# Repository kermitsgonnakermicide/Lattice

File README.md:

# Lattice

> a 60% mechanical keyboard with magnetically attached modules

# what even is Lattice?
Lattice is a modular 60% mechanical keyboard, with the main keyboard featuring:
- cherry mx black switches
- a raspberry pi pico 2
- an EC11 encoder
- 6 expansion ports(two 2.54 inch female headers and 4 4 pin magnetic pogo connectors)
- absolutely NO RGB(in the keyboard itself skdsks)

Lattice also comes with three modules(as of now), which are:
- a 16 key macropad with an OLED

- a 3 slider, two encoder module i'm calling the sliderpad

- a 32x4 RGB LED(specifically the WS2812B-2020) matrix that slides in the empty top bit of the keyboard(connected by 2.54 mm pins because I didnt trust the current limits of the magnetic connectors)

Each module features a xiao rp2040 to run everything else on it because its so smol and cute :3</br>

The macropad and the sliderpad connect with magnetic pogo pins and use I2C to communicate with the main board, while the matrix does the same thing but just connects with normal pin headers and sockets. </br>

in terms of firmware, I have something basic for now - which runs each individual board and packs the data for I2C into a 16 bit struct - this wasnt really tracked as I lowk forgot and I used a bunch of AI so I wouldnt want track it anyways

# why did you even build this?(and many other whys)
I lowkenuinely just needed a keyboard pretty desperately - i've been using my crusty musty dusty redragon k552 for almost 5 years now and I need to switch it out :cryin:
additionally, I wanted a keyboard that I could actually take places, so things like a detachable cable(made possible by the pico 2) and a small form factor without compromising on key count was pretty important to me(hence the modules)

**Q: why xiao rp2040s on each board????**<br>
A: I can get them for hella cheap, they're really well documented, i've worked with them before and they're really small(works well for my purposes)

**Q: why not integrate a microcontroller on your board**<br>
A: while I would love to not use a module and put the straight microcontroller on this board, money is a problem here and I want to try and minimize costs where I can - a PCBA costs a crazy amount of money and with customs and shipping, this project aint covering it :cryin:

**Q: why not RGB?? are you not gamer???**<br>
A: i dont like RGB on the keeb - its annoying to work with, solder and must I remind you - **expensive** - to satiate the thirst for RGB i'm instead just slapping a giant matrix on the top empty bit of the board(hopefully playing snek on it soon)

# build instructions
- print out all PCBs from JLCPCB(only for the matrix PCB, use ENIG as you'll be soldering it yourself)
- get to soldering! a hot air gun/hotplate is reccomended for the matrix
- print out all parts in Production/Prints
- assemble with m3 nuts and bolts
- flash all xiao rp2040s and pico with micropython 
- on all, have boot.py and common.py and use the main.py in each folder for each respective bit 
- connect together and to your computer and start typing!
# images
<details>
<summary> Schematics </summary>

> main keyboard

>macropad 

> sliderpad

> matrix

</details>

<details>

<summary> PCBs </summary>

> main keyboard

> macropad

> sliderpad

> LED matrix

</details>

<details>

<summary> 3D models </summary>

> main keyboard

> macropad

> sliderpad

> LED matrix

</details>

<details>

<summary> CAD renders </summary>

> main keyboard

> macropad

> sliderpad

> the assembled keyboard!

</details>

# Zine

# BOM
| ITEM                          | LINK                                                                                                                                                                                                                                                                                                                                                                                                                                                                                                                                                                                                                                                                                                                                                                                                                                                                                                                                                                                                                                                                                                                                                                             | UNIT PRICE | QTY  | TOTAL PRICE | RUNNING TOTAL | NOTES                                                            |
| ----------------------------- | -------------------------------------------------------------------------------------------------------------------------------------------------------------------------------------------------------------------------------------------------------------------------------------------------------------------------------------------------------------------------------------------------------------------------------------------------------------------------------------------------------------------------------------------------------------------------------------------------------------------------------------------------------------------------------------------------------------------------------------------------------------------------------------------------------------------------------------------------------------------------------------------------------------------------------------------------------------------------------------------------------------------------------------------------------------------------------------------------------------------------------------------------------------------------------- | ---------- | ---- | ----------- | ------------- | ---------------------------------------------------------------- |
| Cherry MX Black Switches      | [https://neomacro.in/products/cherry-mx-switches](https://neomacro.in/products/cherry-mx-switches)                                                                                                                                                                                                                                                                                                                                                                                                                                                                                                                                                                                                                                                                                                                                                                                                                                                                                                                                                                                                                                                                               | 3.51       | 8    | 28.08       | 28.08         | pack of 10                                                       |
| Keycap Set                    | [https://meckeys.com/shop/accessories/keyboard-accessories/keycaps/white-grey-keycaps/](https://meckeys.com/shop/accessories/keyboard-accessories/keycaps/white-grey-keycaps/)                                                                                                                                                                                                                                                                                                                                                                                                                                                                                                                                                                                                                                                                                                                                                                                                                                                                                                                                                                                                   | 10.49      | 1    | 10.49       | 38.57         | for keyboard                                                     |
| Blank Keycaps                 | [https://meckeys.com/shop/accessories/keyboard-accessories/keycaps/blank/blank-dsa-keycaps-1u/](https://meckeys.com/shop/accessories/keyboard-accessories/keycaps/blank/blank-dsa-keycaps-1u/)                                                                                                                                                                                                                                                                                                                                                                                                                                                                                                                                                                                                                                                                                                                                                                                                                                                                                                                                                                                   | 1.05       | 4    | 4.2         | 42.77         | for macropad, will re-use hackpad keycaps                        |
| EC11 Encoders                 | [https://www.amazon.in/CentIoT-Encoder-Digital-Potentiometer-Control/dp/B0888RWNM1?crid=243T1VPT812XT&dib=eyJ2IjoiMSJ9.cvB_S8-clwOY-fsh1jDEgdcKAdzY4Nv9KcBVsP_XLVRbEQ6v9pWSfdi6pitVyRPy5_iq-LYSO24WXsw22WOUBHiEFeP9N0__QSmFXXcr_OLQtUAA2f_e3-WLJc0WOyvXtuYeXFVcwnZSIHdgY8HUAiBYdGh2xdjBK8FlsXImh0q4vkDoK-QkVKE3ac8hCBKdF6XJ_k65GqGC4-3qzPH49GIBedFxUU8WMVSal15O1mF876LbmOvkPvdrdTHcJmVf7XgMnL2mbmJ7N0VyJ4bqivJS2Slw9SVVXHW7uuvRr1E.vdIwwapIw50QxzlGlNGifWW_KbD3sPBQ2U9RfnQ-5LE&dib_tag=se&keywords=EC11+encoder&qid=1780688877&s=industrial&sprefix=ec11+enco%2Cindustrial%2C291&sr=1-1](https://www.amazon.in/CentIoT-Encoder-Digital-Potentiometer-Control/dp/B0888RWNM1?crid=243T1VPT812XT&dib=eyJ2IjoiMSJ9.cvB_S8-clwOY-fsh1jDEgdcKAdzY4Nv9KcBVsP_XLVRbEQ6v9pWSfdi6pitVyRPy5_iq-LYSO24WXsw22WOUBHiEFeP9N0__QSmFXXcr_OLQtUAA2f_e3-WLJc0WOyvXtuYeXFVcwnZSIHdgY8HUAiBYdGh2xdjBK8FlsXImh0q4vkDoK-QkVKE3ac8hCBKdF6XJ_k65GqGC4-3qzPH49GIBedFxUU8WMVSal15O1mF876LbmOvkPvdrdTHcJmVf7XgMnL2mbmJ7N0VyJ4bqivJS2Slw9SVVXHW7uuvRr1E.vdIwwapIw50QxzlGlNGifWW_KbD3sPBQ2U9RfnQ-5LE&dib_tag=se&keywords=EC11+encoder&qid=1780688877&s=industrial&sprefix=ec11+enco%2Cindustrial%2C291&sr=1-1) | 1.8        | 3    | 5.4         | 48.17         | already have                                                     |
| Slide Potentiometers          | [https://www.amazon.in/Electronic-Spices-SC6080GH-Channel-Potentiometer/dp/B0BGY5C2KV?th=1](https://www.amazon.in/Electronic-Spices-SC6080GH-Channel-Potentiometer/dp/B0BGY5C2KV?th=1)                                                                                                                                                                                                                                                                                                                                                                                                                                                                                                                                                                                                                                                                                                                                                                                                                                                                                                                                                                                           | 3          | 1.68 | 5.04        | 53.21         | amazon is unfortunately the cheapest and most reliable place >:( |
| OLED                          | [https://robu.in/product/0-96-inch-i2c-iic-oled-lcd-module-4pin-with-vcc-gnd-blue/](https://robu.in/product/0-96-inch-i2c-iic-oled-lcd-module-4pin-with-vcc-gnd-blue/)                                                                                                                                                                                                                                                                                                                                                                                                                                                                                                                                                                                                                                                                                                                                                                                                                                                                                                                                                                                                           | 2.14       | 1    | 2.14        | 55.35         | already have                                                     |
| 1N4148 diodes                 | [https://robu.in/product/1n4148-1w-zener-diode-pack-of-50/](https://robu.in/product/1n4148-1w-zener-diode-pack-of-50/)                                                                                                                                                                                                                                                                                                                                                                                                                                                                                                                                                                                                                                                                                                                                                                                                                                                                                                                                                                                                                                                           | 0.013      | 80   | 1.04        | 56.39         |                                                                  |
| PCB                           | JLCPCB                                                                                                                                                                                                                                                                                                                                                                                                                                                                                                                                                                                                                                                                                                                                                                                                                                                                                                                                                                                                                                                                                                                                                                           | 82.42      | 1    | 82.42       | 138.81        |                                                                  |
| Xiao RP2040                   | [https://thinkrobotics.com/products/seeed-studio-xiao-rp2040?variant=47933480173885&country=IN&currency=INR&utm_medium=product_sync&utm_source=google&utm_content=sag_organic&utm_campaign=sag_organic](https://thinkrobotics.com/products/seeed-studio-xiao-rp2040?variant=47933480173885&country=IN&currency=INR&utm_medium=product_sync&utm_source=google&utm_content=sag_organic&utm_campaign=sag_organic)                                                                                                                                                                                                                                                                                                                                                                                                                                                                                                                                                                                                                                                                                                                                                                   | 5.77       | 3    | 17.31       | 156.12        | already have 2                                                   |
| Pico 2                        | [https://robu.in/product/raspberry-pi-pico-2/](https://robu.in/product/raspberry-pi-pico-2/)                                                                                                                                                                                                                                                                                                                                                                                                                                                                                                                                                                                                                                                                                                                                                                                                                                                                                                                                                                                                                                                                                     | 5.7        | 1    | 5.7         | 161.82        | already have 2                                                   |
| WS2812B                       | [https://hubtronics.in/ws2812b-2020](https://hubtronics.in/ws2812b-2020)                                                                                                                                                                                                                                                                                                                                                                                                                                                                                                                                                                                                                                                                                                                                                                                                                                                                                                                                                                                                                                                                                                         | 0.06       | 128  | 7.68        | 169.5         |                                                                  |
| 4 pin magnetic connector pair | [https://www.flyrobo.in/4pin-pogo-magnetic-connector-pair?srsltid=AfmBOooMbv4sQ4AFQ2Pcy11oPOmPRyrziCGq09HopU752agqQ4loADge](https://www.flyrobo.in/4pin-pogo-magnetic-connector-pair?srsltid=AfmBOooMbv4sQ4AFQ2Pcy11oPOmPRyrziCGq09HopU752agqQ4loADge)                                                                                                                                                                                                                                                                                                                                                                                                                                                                                                                                                                                                                                                                                                                                                                                                                                                                                                                           | 2.06       | 4    | 8.24        | 177.74        |                                                                  |
| TOTAL                         |                                                                                                                                                                                                                                                                                                                                                                                                                                                                                                                                                                                                                                                                                                                                                                                                                                                                                                                                                                                                                                                                                                                                                                                  |            |      | 0           | 177.74        |                                                                  |

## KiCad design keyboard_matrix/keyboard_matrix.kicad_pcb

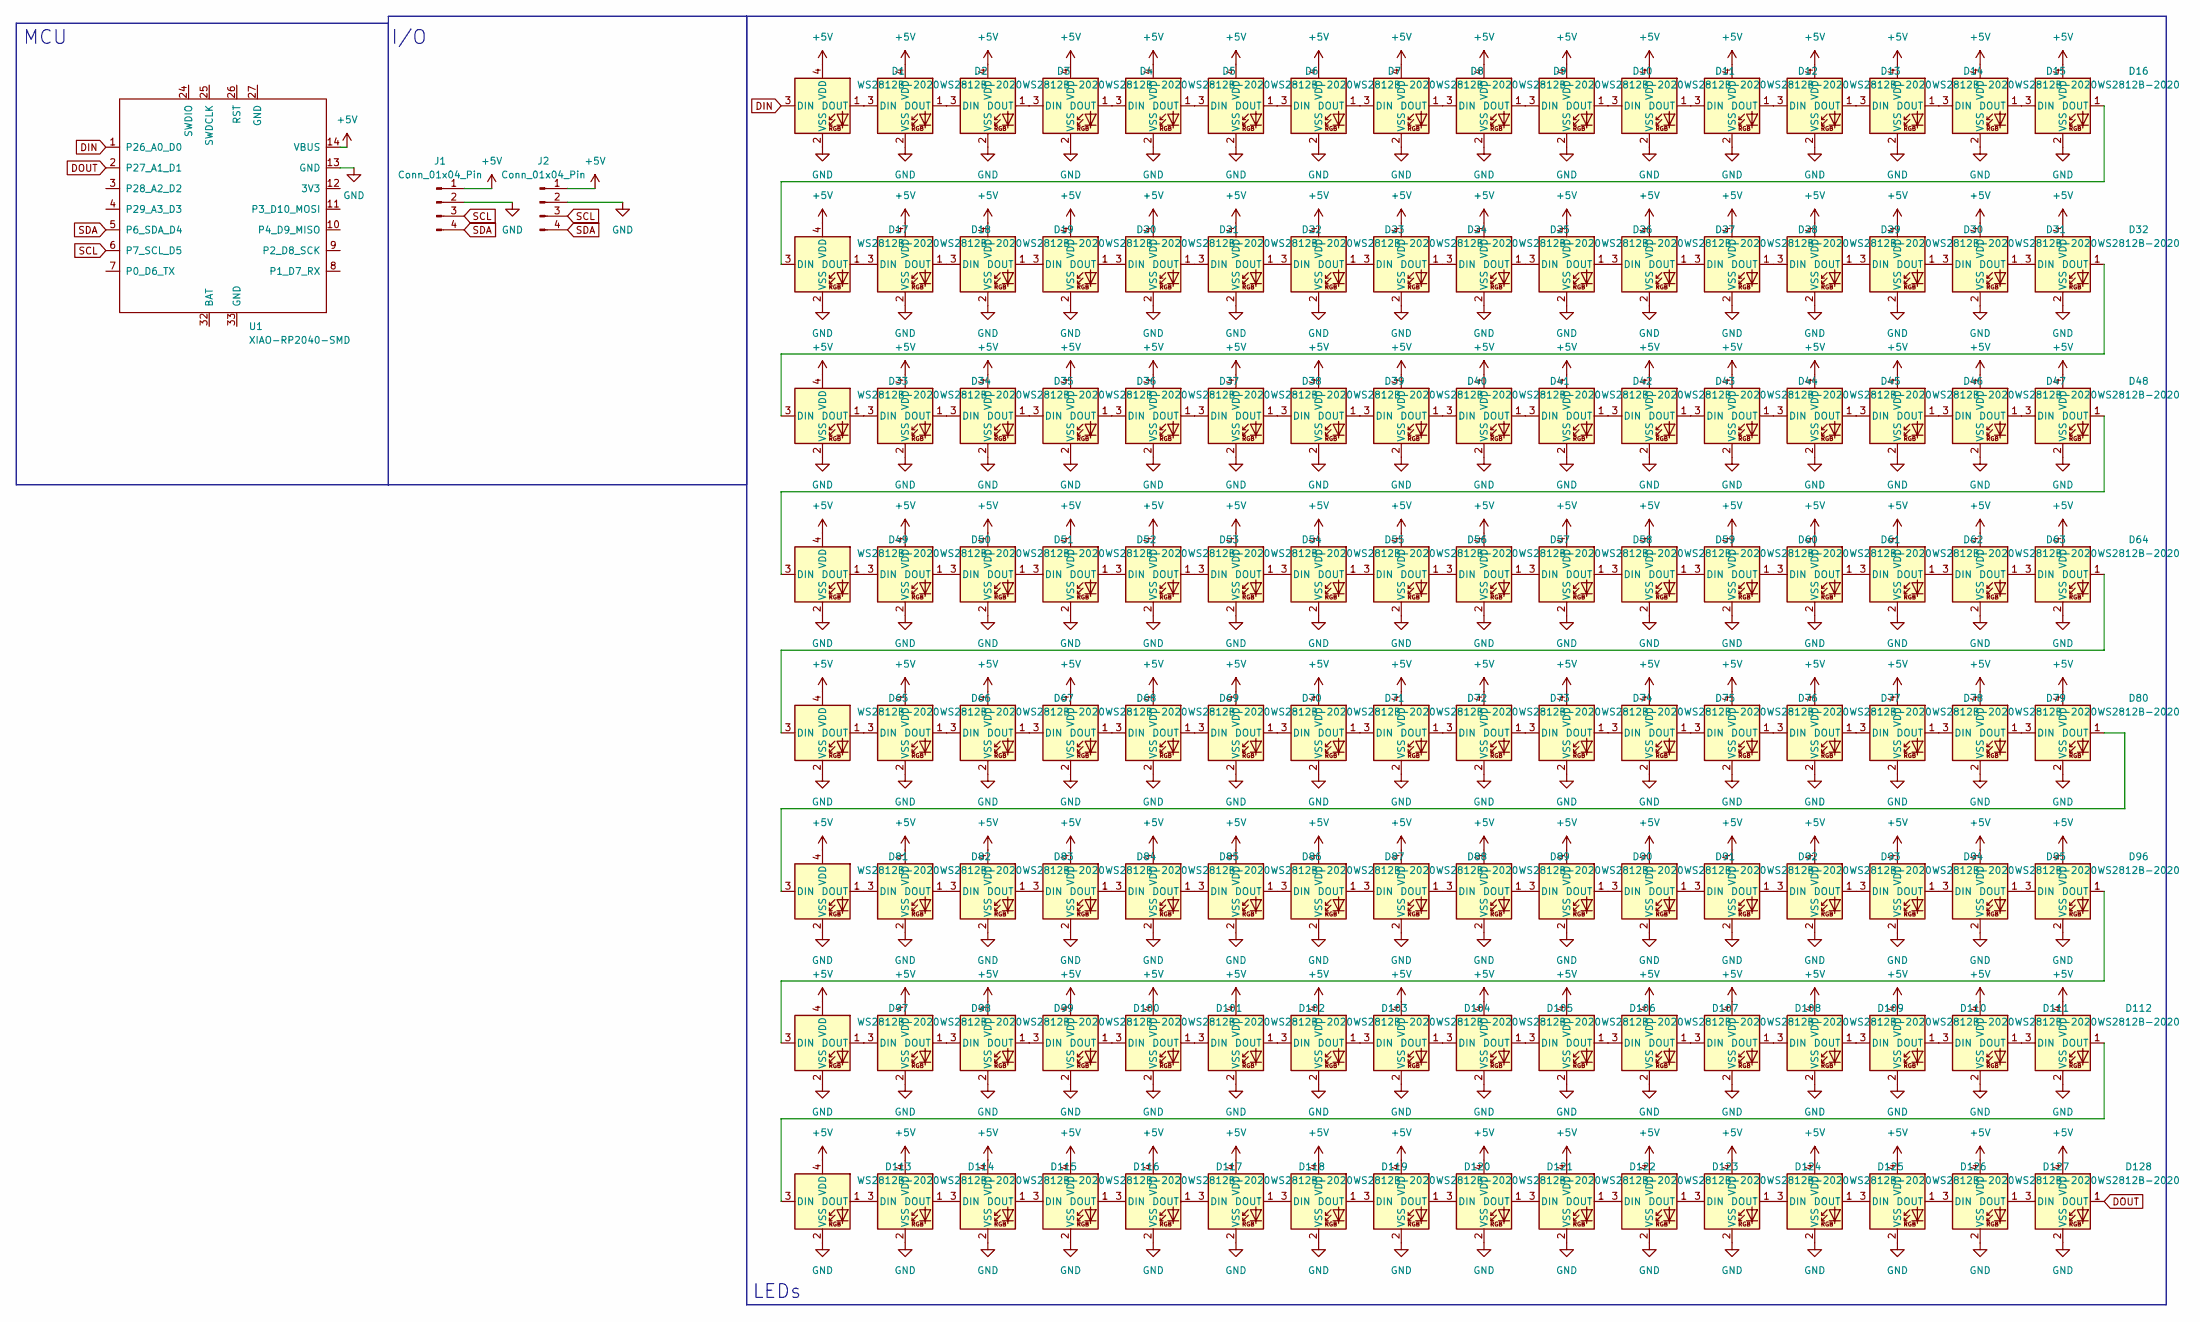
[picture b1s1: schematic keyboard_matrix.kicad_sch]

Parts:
D1, D2, D3, D4, D5, D6, D7, D8, D9, D10, D11, D12, D13, D14, D15, D16, D17, D18, D19, D20, D21, D22, D23, D24, D25, D26, D27, D28, D29, D30, D31, D32, D33, D34, D35, D36, D37, D38, D39, D40, D41, D42, D43, D44, D45, D46, D47, D48, D49, D50, D51, D52, D53, D54, D55, D56, D57, D58, D59, D60, D61, D62, D63, D64, D65, D66, D67, D68, D69, D70, D71, D72, D73, D74, D75, D76, D77, D78, D79, D80, D81, D82, D83, D84, D85, D86, D87, D88, D89, D90, D91, D92, D93, D94, D95, D96, D97, D98, D99, D100, D101, D102, D103, D104, D105, D106, D107, D108, D109, D110, D111, D112, D113, D114, D115, D116, D117, D118, D119, D120, D121, D122, D123, D124, D125, D126, D127, D128: WS2812B-2020; LED_WS2812B-2020_PLCC4_2.0x2.0mm
J1, J2: Conn_01x04_Pin; PinHeader_1x04_P2.54mm_Vertical_SMD_Pin1Right
U1: XIAO-RP2040-SMD

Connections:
+5V: D1.4 (VDD), D2.4 (VDD), D3.4 (VDD), D4.4 (VDD), D5.4 (VDD), D6.4 (VDD), D7.4 (VDD), D8.4 (VDD), D9.4 (VDD), D10.4 (VDD), D11.4 (VDD), D12.4 (VDD), D13.4 (VDD), D14.4 (VDD), D15.4 (VDD), D16.4 (VDD), D17.4 (VDD), D18.4 (VDD), D19.4 (VDD), D20.4 (VDD), D21.4 (VDD), D22.4 (VDD), D23.4 (VDD), D24.4 (VDD), D25.4 (VDD), D26.4 (VDD), D27.4 (VDD), D28.4 (VDD), D29.4 (VDD), D30.4 (VDD), D31.4 (VDD), D32.4 (VDD), D33.4 (VDD), D34.4 (VDD), D35.4 (VDD), D36.4 (VDD), D37.4 (VDD), D38.4 (VDD), D39.4 (VDD), D40.4 (VDD), D41.4 (VDD), D42.4 (VDD), D43.4 (VDD), D44.4 (VDD), D45.4 (VDD), D46.4 (VDD), D47.4 (VDD), D48.4 (VDD), D49.4 (VDD), D50.4 (VDD), D51.4 (VDD), D52.4 (VDD), D53.4 (VDD), D54.4 (VDD), D55.4 (VDD), D56.4 (VDD), D57.4 (VDD), D58.4 (VDD), D59.4 (VDD), D60.4 (VDD), D61.4 (VDD), D62.4 (VDD), D63.4 (VDD), D64.4 (VDD), D65.4 (VDD), D66.4 (VDD), D67.4 (VDD), D68.4 (VDD), D69.4 (VDD), D70.4 (VDD), D71.4 (VDD), D72.4 (VDD), D73.4 (VDD), D74.4 (VDD), D75.4 (VDD), D76.4 (VDD), D77.4 (VDD), D78.4 (VDD), D79.4 (VDD), D80.4 (VDD), D81.4 (VDD), D82.4 (VDD), D83.4 (VDD), D84.4 (VDD), D85.4 (VDD), D86.4 (VDD), D87.4 (VDD), D88.4 (VDD), D89.4 (VDD), D90.4 (VDD), D91.4 (VDD), D92.4 (VDD), D93.4 (VDD), D94.4 (VDD), D95.4 (VDD), D96.4 (VDD), D97.4 (VDD), D98.4 (VDD), D99.4 (VDD), D100.4 (VDD), D101.4 (VDD), D102.4 (VDD), D103.4 (VDD), D104.4 (VDD), D105.4 (VDD), D106.4 (VDD), D107.4 (VDD), D108.4 (VDD), D109.4 (VDD), D110.4 (VDD), D111.4 (VDD), D112.4 (VDD), D113.4 (VDD), D114.4 (VDD), D115.4 (VDD), D116.4 (VDD), D117.4 (VDD), D118.4 (VDD), D119.4 (VDD), D120.4 (VDD), D121.4 (VDD), D122.4 (VDD), D123.4 (VDD), D124.4 (VDD), D125.4 (VDD), D126.4 (VDD), D127.4 (VDD), D128.4 (VDD), J1.1, J2.1, U1.14 (VBUS)
DIN: D1.3 (DIN), U1.1 (P26_A0_D0)
DOUT: D128.1 (DOUT), U1.2 (P27_A1_D1)
GND: D1.2 (VSS), D2.2 (VSS), D3.2 (VSS), D4.2 (VSS), D5.2 (VSS), D6.2 (VSS), D7.2 (VSS), D8.2 (VSS), D9.2 (VSS), D10.2 (VSS), D11.2 (VSS), D12.2 (VSS), D13.2 (VSS), D14.2 (VSS), D15.2 (VSS), D16.2 (VSS), D17.2 (VSS), D18.2 (VSS), D19.2 (VSS), D20.2 (VSS), D21.2 (VSS), D22.2 (VSS), D23.2 (VSS), D24.2 (VSS), D25.2 (VSS), D26.2 (VSS), D27.2 (VSS), D28.2 (VSS), D29.2 (VSS), D30.2 (VSS), D31.2 (VSS), D32.2 (VSS), D33.2 (VSS), D34.2 (VSS), D35.2 (VSS), D36.2 (VSS), D37.2 (VSS), D38.2 (VSS), D39.2 (VSS), D40.2 (VSS), D41.2 (VSS), D42.2 (VSS), D43.2 (VSS), D44.2 (VSS), D45.2 (VSS), D46.2 (VSS), D47.2 (VSS), D48.2 (VSS), D49.2 (VSS), D50.2 (VSS), D51.2 (VSS), D52.2 (VSS), D53.2 (VSS), D54.2 (VSS), D55.2 (VSS), D56.2 (VSS), D57.2 (VSS), D58.2 (VSS), D59.2 (VSS), D60.2 (VSS), D61.2 (VSS), D62.2 (VSS), D63.2 (VSS), D64.2 (VSS), D65.2 (VSS), D66.2 (VSS), D67.2 (VSS), D68.2 (VSS), D69.2 (VSS), D70.2 (VSS), D71.2 (VSS), D72.2 (VSS), D73.2 (VSS), D74.2 (VSS), D75.2 (VSS), D76.2 (VSS), D77.2 (VSS), D78.2 (VSS), D79.2 (VSS), D80.2 (VSS), D81.2 (VSS), D82.2 (VSS), D83.2 (VSS), D84.2 (VSS), D85.2 (VSS), D86.2 (VSS), D87.2 (VSS), D88.2 (VSS), D89.2 (VSS), D90.2 (VSS), D91.2 (VSS), D92.2 (VSS), D93.2 (VSS), D94.2 (VSS), D95.2 (VSS), D96.2 (VSS), D97.2 (VSS), D98.2 (VSS), D99.2 (VSS), D100.2 (VSS), D101.2 (VSS), D102.2 (VSS), D103.2 (VSS), D104.2 (VSS), D105.2 (VSS), D106.2 (VSS), D107.2 (VSS), D108.2 (VSS), D109.2 (VSS), D110.2 (VSS), D111.2 (VSS), D112.2 (VSS), D113.2 (VSS), D114.2 (VSS), D115.2 (VSS), D116.2 (VSS), D117.2 (VSS), D118.2 (VSS), D119.2 (VSS), D120.2 (VSS), D121.2 (VSS), D122.2 (VSS), D123.2 (VSS), D124.2 (VSS), D125.2 (VSS), D126.2 (VSS), D127.2 (VSS), D128.2 (VSS), J1.2, J2.2, U1.13 (GND)
unnamed: D1.1 (DOUT), D2.3 (DIN)
unnamed: D2.1 (DOUT), D3.3 (DIN)
unnamed: D3.1 (DOUT), D4.3 (DIN)
unnamed: D4.1 (DOUT), D5.3 (DIN)
unnamed: D5.1 (DOUT), D6.3 (DIN)
unnamed: D6.1 (DOUT), D7.3 (DIN)
unnamed: D7.1 (DOUT), D8.3 (DIN)
unnamed: D8.1 (DOUT), D9.3 (DIN)
unnamed: D9.1 (DOUT), D10.3 (DIN)
unnamed: D10.1 (DOUT), D11.3 (DIN)
unnamed: D11.1 (DOUT), D12.3 (DIN)
unnamed: D12.1 (DOUT), D13.3 (DIN)
unnamed: D13.1 (DOUT), D14.3 (DIN)
unnamed: D14.1 (DOUT), D15.3 (DIN)
unnamed: D15.1 (DOUT), D16.3 (DIN)
unnamed: D16.1 (DOUT), D17.3 (DIN)
unnamed: D17.1 (DOUT), D18.3 (DIN)
unnamed: D18.1 (DOUT), D19.3 (DIN)
unnamed: D19.1 (DOUT), D20.3 (DIN)
unnamed: D20.1 (DOUT), D21.3 (DIN)
unnamed: D21.1 (DOUT), D22.3 (DIN)
unnamed: D22.1 (DOUT), D23.3 (DIN)
unnamed: D23.1 (DOUT), D24.3 (DIN)
unnamed: D24.1 (DOUT), D25.3 (DIN)
unnamed: D25.1 (DOUT), D26.3 (DIN)
unnamed: D26.1 (DOUT), D27.3 (DIN)
unnamed: D27.1 (DOUT), D28.3 (DIN)
unnamed: D28.1 (DOUT), D29.3 (DIN)
unnamed: D29.1 (DOUT), D30.3 (DIN)
unnamed: D30.1 (DOUT), D31.3 (DIN)
unnamed: D31.1 (DOUT), D32.3 (DIN)
unnamed: D32.1 (DOUT), D33.3 (DIN)
unnamed: D33.1 (DOUT), D34.3 (DIN)
unnamed: D34.1 (DOUT), D35.3 (DIN)
unnamed: D35.1 (DOUT), D36.3 (DIN)
unnamed: D36.1 (DOUT), D37.3 (DIN)
unnamed: D37.1 (DOUT), D38.3 (DIN)
unnamed: D38.1 (DOUT), D39.3 (DIN)
unnamed: D39.1 (DOUT), D40.3 (DIN)
unnamed: D40.1 (DOUT), D41.3 (DIN)
unnamed: D41.1 (DOUT), D42.3 (DIN)
unnamed: D42.1 (DOUT), D43.3 (DIN)
unnamed: D43.1 (DOUT), D44.3 (DIN)
unnamed: D44.1 (DOUT), D45.3 (DIN)
unnamed: D45.1 (DOUT), D46.3 (DIN)
unnamed: D46.1 (DOUT), D47.3 (DIN)
unnamed: D47.1 (DOUT), D48.3 (DIN)
unnamed: D48.1 (DOUT), D49.3 (DIN)
unnamed: D49.1 (DOUT), D50.3 (DIN)
unnamed: D50.1 (DOUT), D51.3 (DIN)
unnamed: D51.1 (DOUT), D52.3 (DIN)
unnamed: D52.1 (DOUT), D53.3 (DIN)
unnamed: D53.1 (DOUT), D54.3 (DIN)
unnamed: D54.1 (DOUT), D55.3 (DIN)
unnamed: D55.1 (DOUT), D56.3 (DIN)
unnamed: D56.1 (DOUT), D57.3 (DIN)
unnamed: D57.1 (DOUT), D58.3 (DIN)
unnamed: D58.1 (DOUT), D59.3 (DIN)
unnamed: D59.1 (DOUT), D60.3 (DIN)
unnamed: D60.1 (DOUT), D61.3 (DIN)
unnamed: D61.1 (DOUT), D62.3 (DIN)
unnamed: D62.1 (DOUT), D63.3 (DIN)
unnamed: D63.1 (DOUT), D64.3 (DIN)
unnamed: D64.1 (DOUT), D65.3 (DIN)
unnamed: D65.1 (DOUT), D66.3 (DIN)
unnamed: D66.1 (DOUT), D67.3 (DIN)
unnamed: D67.1 (DOUT), D68.3 (DIN)
unnamed: D68.1 (DOUT), D69.3 (DIN)
unnamed: D69.1 (DOUT), D70.3 (DIN)
unnamed: D70.1 (DOUT), D71.3 (DIN)
unnamed: D71.1 (DOUT), D72.3 (DIN)
unnamed: D72.1 (DOUT), D73.3 (DIN)
unnamed: D73.1 (DOUT), D74.3 (DIN)
unnamed: D74.1 (DOUT), D75.3 (DIN)
unnamed: D75.1 (DOUT), D76.3 (DIN)
unnamed: D76.1 (DOUT), D77.3 (DIN)
unnamed: D77.1 (DOUT), D78.3 (DIN)
unnamed: D78.1 (DOUT), D79.3 (DIN)
unnamed: D79.1 (DOUT), D80.3 (DIN)
unnamed: D80.1 (DOUT), D81.3 (DIN)
unnamed: D81.1 (DOUT), D82.3 (DIN)
unnamed: D82.1 (DOUT), D83.3 (DIN)
unnamed: D83.1 (DOUT), D84.3 (DIN)
unnamed: D84.1 (DOUT), D85.3 (DIN)
unnamed: D85.1 (DOUT), D86.3 (DIN)
unnamed: D86.1 (DOUT), D87.3 (DIN)
unnamed: D87.1 (DOUT), D88.3 (DIN)
unnamed: D88.1 (DOUT), D89.3 (DIN)
unnamed: D89.1 (DOUT), D90.3 (DIN)
unnamed: D90.1 (DOUT), D91.3 (DIN)
unnamed: D91.1 (DOUT), D92.3 (DIN)
unnamed: D92.1 (DOUT), D93.3 (DIN)
unnamed: D93.1 (DOUT), D94.3 (DIN)
unnamed: D94.1 (DOUT), D95.3 (DIN)
unnamed: D95.1 (DOUT), D96.3 (DIN)
unnamed: D96.1 (DOUT), D97.3 (DIN)
unnamed: D97.1 (DOUT), D98.3 (DIN)
unnamed: D98.1 (DOUT), D99.3 (DIN)
unnamed: D99.1 (DOUT), D100.3 (DIN)
unnamed: D100.1 (DOUT), D101.3 (DIN)
unnamed: D101.1 (DOUT), D102.3 (DIN)
unnamed: D102.1 (DOUT), D103.3 (DIN)
unnamed: D103.1 (DOUT), D104.3 (DIN)
unnamed: D104.1 (DOUT), D105.3 (DIN)
unnamed: D105.1 (DOUT), D106.3 (DIN)
unnamed: D106.1 (DOUT), D107.3 (DIN)
unnamed: D107.1 (DOUT), D108.3 (DIN)
unnamed: D108.1 (DOUT), D109.3 (DIN)
unnamed: D109.1 (DOUT), D110.3 (DIN)
unnamed: D110.1 (DOUT), D111.3 (DIN)
unnamed: D111.1 (DOUT), D112.3 (DIN)
unnamed: D112.1 (DOUT), D113.3 (DIN)
unnamed: D113.1 (DOUT), D114.3 (DIN)
unnamed: D114.1 (DOUT), D115.3 (DIN)
unnamed: D115.1 (DOUT), D116.3 (DIN)
unnamed: D116.1 (DOUT), D117.3 (DIN)
unnamed: D117.1 (DOUT), D118.3 (DIN)
unnamed: D118.1 (DOUT), D119.3 (DIN)
unnamed: D119.1 (DOUT), D120.3 (DIN)
unnamed: D120.1 (DOUT), D121.3 (DIN)
unnamed: D121.1 (DOUT), D122.3 (DIN)
unnamed: D122.1 (DOUT), D123.3 (DIN)
unnamed: D123.1 (DOUT), D124.3 (DIN)
unnamed: D124.1 (DOUT), D125.3 (DIN)
unnamed: D125.1 (DOUT), D126.3 (DIN)
unnamed: D126.1 (DOUT), D127.3 (DIN)
unnamed: D127.1 (DOUT), D128.3 (DIN)
SCL: J1.3, J2.3, U1.6 (P7_SCL_D5)
SDA: J1.4, J2.4, U1.5 (P6_SDA_D4)

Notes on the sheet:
LEDs
MCU
I/O

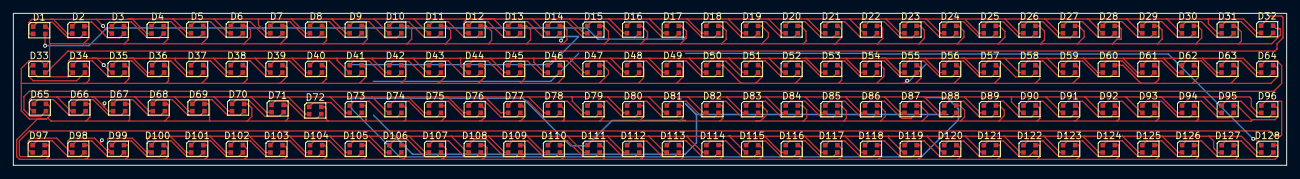
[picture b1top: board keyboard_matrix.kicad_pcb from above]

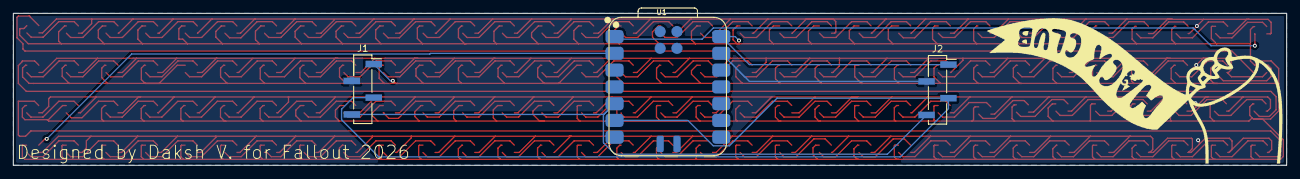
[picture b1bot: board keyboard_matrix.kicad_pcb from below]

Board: 2 copper layers, 192.8 x 23.0 mm, 131 parts (3 on the bottom side), 133 nets.

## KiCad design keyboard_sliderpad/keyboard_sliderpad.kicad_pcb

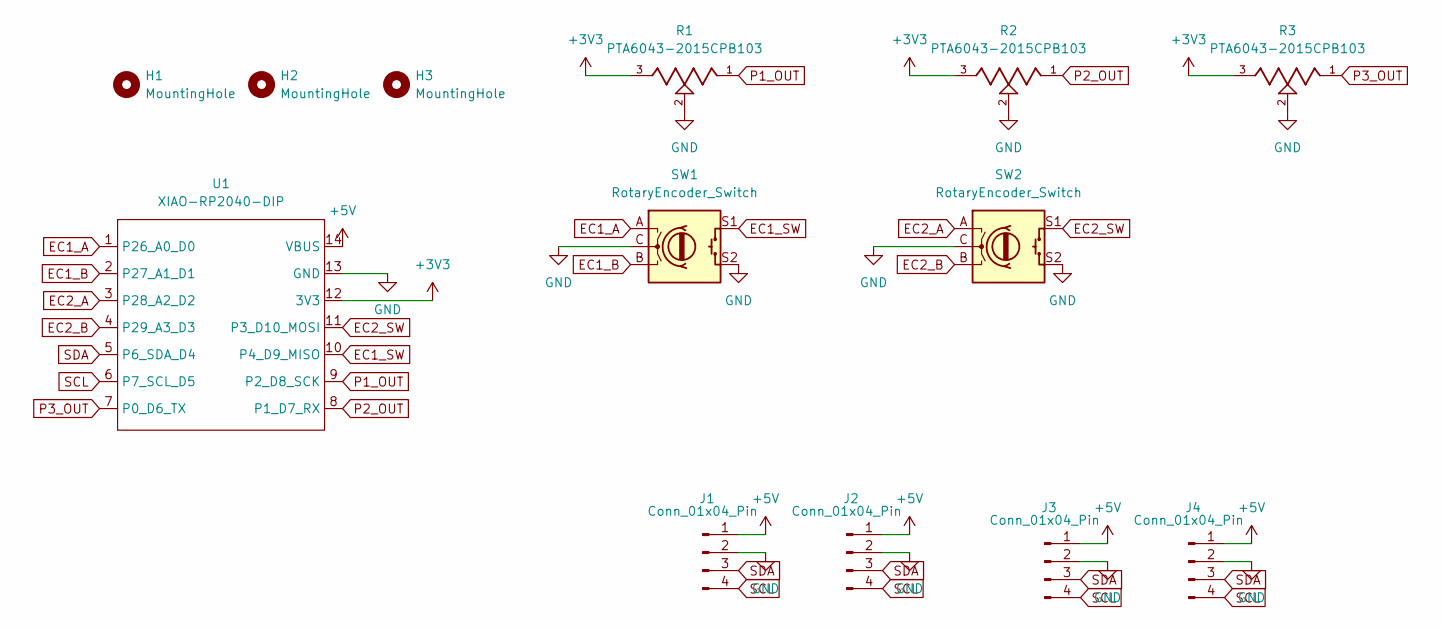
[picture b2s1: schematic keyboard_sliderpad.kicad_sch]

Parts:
H1, H2, H3: MountingHole; MountingHole_3.2mm_M3
J1, J2, J3, J4: Conn_01x04_Pin; PinSocket_1x04_P2.54mm_Vertical
R1, R2, R3: PTA6043-2015CPB103; TRIM_PTA6043-2015CPB103; PARTREV 04/21
SW1, SW2: RotaryEncoder_Switch; RotaryEncoder_Alps_EC11E-Switch_Vertical_H20mm
U1: XIAO-RP2040-DIP

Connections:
+3V3: R1.3, R2.3, R3.3, U1.12 (3V3)
+5V: J1.1, J2.1, J3.1, J4.1, U1.14 (VBUS)
EC1_A: SW1.A, U1.1 (P26_A0_D0)
EC1_B: SW1.B, U1.2 (P27_A1_D1)
EC1_SW: SW1.S1, U1.10 (P4_D9_MISO)
EC2_A: SW2.A, U1.3 (P28_A2_D2)
EC2_B: SW2.B, U1.4 (P29_A3_D3)
EC2_SW: SW2.S1, U1.11 (P3_D10_MOSI)
GND: J1.2, J2.2, J3.2, J4.2, R1.2, R2.2, R3.2, SW1.C, SW1.S2, SW2.C, SW2.S2, U1.13 (GND)
P1_OUT: R1.1, U1.9 (P2_D8_SCK)
P2_OUT: R2.1, U1.8 (P1_D7_RX)
P3_OUT: R3.1, U1.7 (P0_D6_TX)
SCL: J1.4, J2.4, J3.4, J4.4, U1.6 (P7_SCL_D5)
SDA: J1.3, J2.3, J3.3, J4.3, U1.5 (P6_SDA_D4)

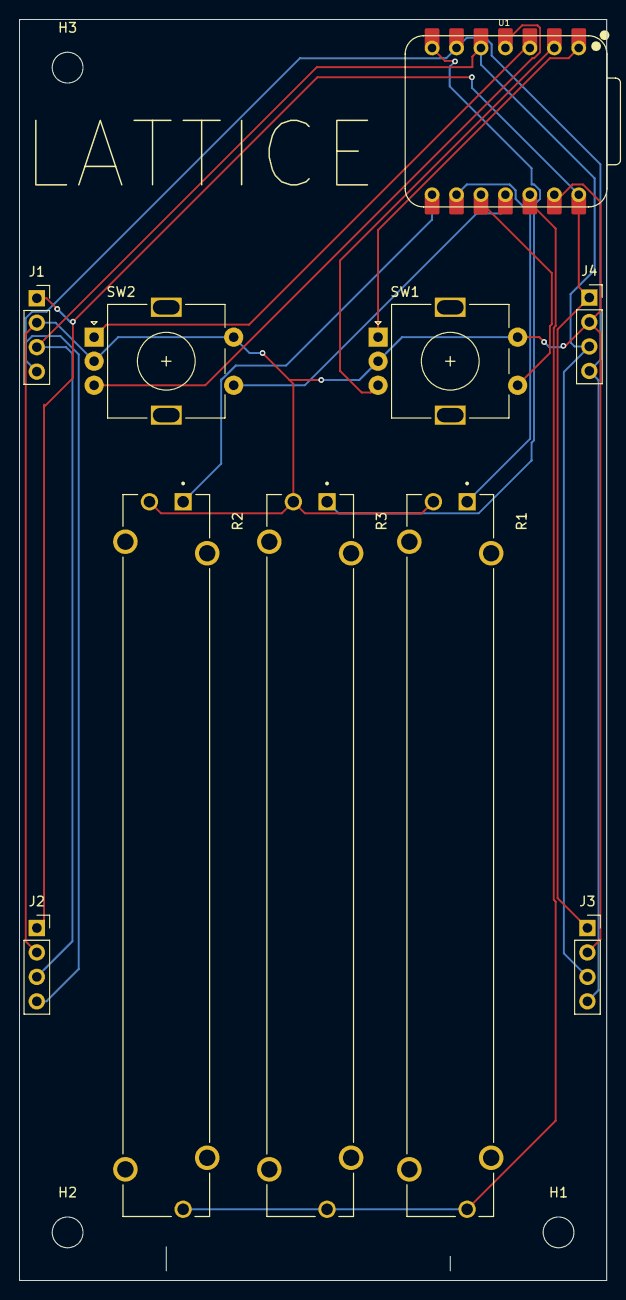
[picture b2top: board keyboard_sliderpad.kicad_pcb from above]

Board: 2 copper layers, 61.0 x 131.0 mm, 13 parts (0 on the bottom side), 14 nets.

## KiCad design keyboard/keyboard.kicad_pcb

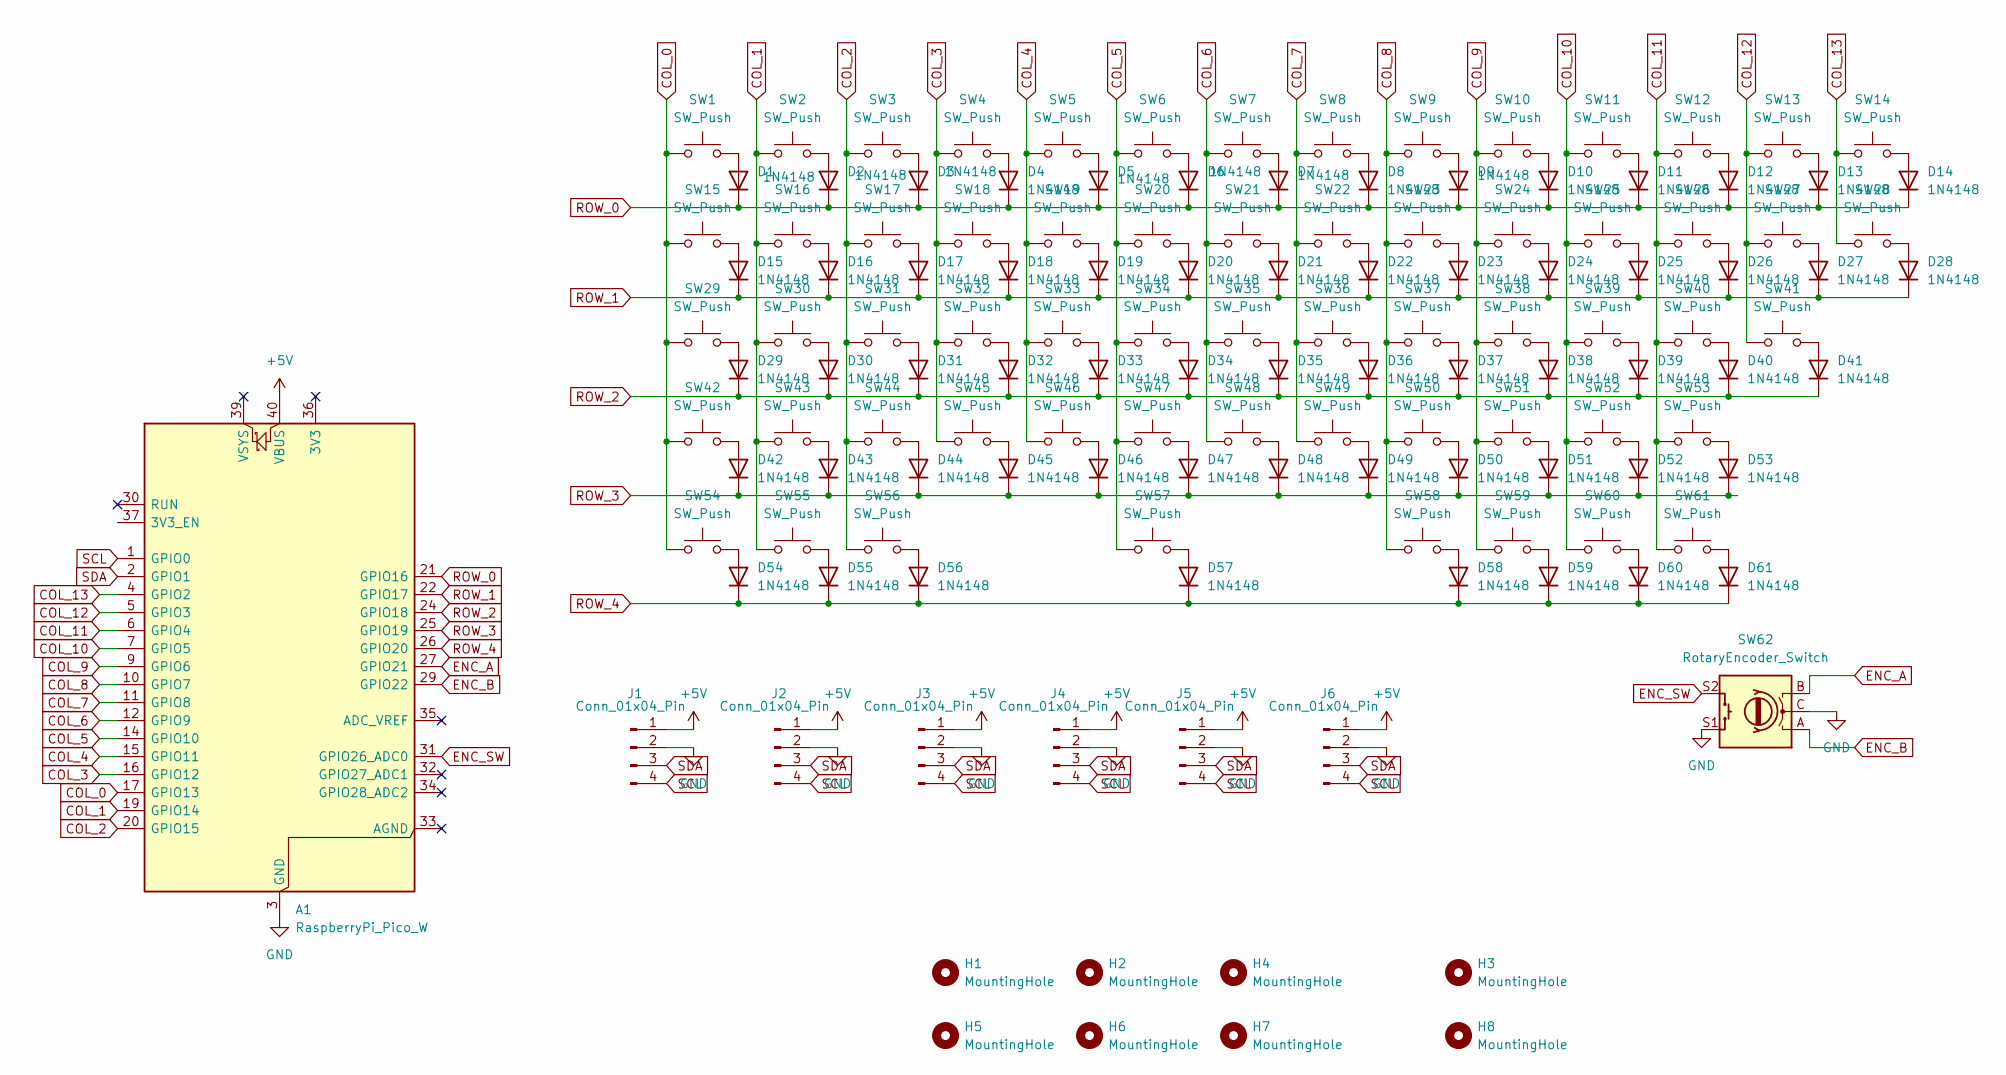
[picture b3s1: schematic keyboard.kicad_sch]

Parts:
A1: RaspberryPi_Pico_W; RaspberryPi_Pico_Common_THT
D1, D2, D3, D4, D5, D6, D7, D8, D9, D10, D11, D12, D13, D14, D15, D16, D17, D18, D19, D20, D21, D22, D23, D24, D25, D26, D27, D28, D29, D30, D31, D32, D33, D34, D35, D36, D37, D38, D39, D40, D41, D42, D43, D44, D45, D46, D47, D48, D49, D50, D51, D52, D53, D54, D55, D56, D57, D58, D59, D60, D61: 1N4148; D_DO-35_SOD27_P7.62mm_Horizontal
H1, H2, H3, H4, H5, H6, H7, H8: MountingHole; MountingHole_3.2mm_M3
J1, J2, J3, J4: Conn_01x04_Pin; PinSocket_1x04_P1.00mm_Vertical
J5, J6: Conn_01x04_Pin; PinSocket_1x04_P2.54mm_Vertical
SW1, SW2, SW3, SW4, SW5, SW6, SW7, SW8, SW9, SW10, SW11, SW12, SW13, SW16, SW17, SW18, SW19, SW20, SW21, SW22, SW23, SW24, SW25, SW26, SW27, SW30, SW31, SW32, SW33, SW34, SW35, SW36, SW37, SW38, SW39, SW40, SW43, SW44, SW45, SW46, SW47, SW48, SW49, SW50, SW51, SW52: SW_Push; SW_Cherry_MX_1.00u_PCB
SW14: SW_Push; SW_Cherry_MX_2.00u_PCB
SW15, SW28: SW_Push; SW_Cherry_MX_1.50u_PCB
SW29: SW_Push; SW_Cherry_MX_1.75u_PCB
SW41, SW42: SW_Push; SW_Cherry_MX_2.25u_PCB
SW53: SW_Push; SW_Cherry_MX_2.75u_PCB
SW54, SW55, SW56, SW58, SW59, SW60, SW61: SW_Push; SW_Cherry_MX_1.25u_PCB
SW57: SW_Push; SW_Cherry_MX_6.25u_PCB
SW62: RotaryEncoder_Switch; RotaryEncoder_Alps_EC11E-Switch_Vertical_H20mm

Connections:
+5V: A1.40 (VBUS), J1.1, J2.1, J3.1, J4.1, J5.1, J6.1
COL_0: A1.17 (GPIO13), SW1.1, SW15.1, SW29.1, SW42.1, SW54.1
COL_1: A1.19 (GPIO14), SW2.1, SW16.1, SW30.1, SW43.1, SW55.1
COL_2: A1.20 (GPIO15), SW3.1, SW17.1, SW31.1, SW44.1, SW56.1
COL_3: A1.16 (GPIO12), SW4.1, SW18.1, SW32.1, SW45.1
COL_4: A1.15 (GPIO11), SW5.1, SW19.1, SW33.1, SW46.1
COL_5: A1.14 (GPIO10), SW6.1, SW20.1, SW34.1, SW47.1, SW57.1
COL_6: A1.12 (GPIO9), SW7.1, SW21.1, SW35.1, SW48.1
COL_7: A1.11 (GPIO8), SW8.1, SW22.1, SW36.1, SW49.1
COL_8: A1.10 (GPIO7), SW9.1, SW23.1, SW37.1, SW50.1, SW58.1
COL_9: A1.9 (GPIO6), SW10.1, SW24.1, SW38.1, SW51.1, SW59.1
COL_10: A1.7 (GPIO5), SW11.1, SW25.1, SW39.1, SW52.1, SW60.1
COL_11: A1.6 (GPIO4), SW12.1, SW26.1, SW40.1, SW53.1, SW61.1
COL_12: A1.5 (GPIO3), SW13.1, SW27.1, SW41.1
COL_13: A1.4 (GPIO2), SW14.1, SW28.1
ENC_A: A1.27 (GPIO21), SW62.B
ENC_B: A1.29 (GPIO22), SW62.A
ENC_SW: A1.31 (GPIO26_ADC0), SW62.S2
GND: A1.3 (GND), A1.8 (GND), A1.13 (GND), A1.18 (GND), A1.23 (GND), A1.28 (GND), A1.38 (GND), J1.2, J2.2, J3.2, J4.2, J5.2, J6.2, SW62.C, SW62.S1
unnamed: D1.2 (A), SW1.2
unnamed: D2.2 (A), SW2.2
unnamed: D3.2 (A), SW3.2
unnamed: D4.2 (A), SW4.2
unnamed: D5.2 (A), SW5.2
unnamed: D6.2 (A), SW6.2
unnamed: D7.2 (A), SW7.2
unnamed: D8.2 (A), SW8.2
unnamed: D9.2 (A), SW9.2
unnamed: D10.2 (A), SW10.2
unnamed: D11.2 (A), SW11.2
unnamed: D12.2 (A), SW12.2
unnamed: D13.2 (A), SW13.2
unnamed: D14.2 (A), SW14.2
unnamed: D15.2 (A), SW15.2
unnamed: D16.2 (A), SW16.2
unnamed: D17.2 (A), SW17.2
unnamed: D18.2 (A), SW18.2
unnamed: D19.2 (A), SW19.2
unnamed: D20.2 (A), SW20.2
unnamed: D21.2 (A), SW21.2
unnamed: D22.2 (A), SW22.2
unnamed: D23.2 (A), SW23.2
unnamed: D24.2 (A), SW24.2
unnamed: D25.2 (A), SW25.2
unnamed: D26.2 (A), SW26.2
unnamed: D27.2 (A), SW27.2
unnamed: D28.2 (A), SW28.2
unnamed: D29.2 (A), SW29.2
unnamed: D30.2 (A), SW30.2
unnamed: D31.2 (A), SW31.2
unnamed: D32.2 (A), SW32.2
unnamed: D33.2 (A), SW33.2
unnamed: D34.2 (A), SW34.2
unnamed: D35.2 (A), SW35.2
unnamed: D36.2 (A), SW36.2
unnamed: D37.2 (A), SW37.2
unnamed: D38.2 (A), SW38.2
unnamed: D39.2 (A), SW39.2
unnamed: D40.2 (A), SW40.2
unnamed: D41.2 (A), SW41.2
unnamed: D42.2 (A), SW42.2
unnamed: D43.2 (A), SW43.2
unnamed: D44.2 (A), SW44.2
unnamed: D45.2 (A), SW45.2
unnamed: D46.2 (A), SW46.2
unnamed: D47.2 (A), SW47.2
unnamed: D48.2 (A), SW48.2
unnamed: D49.2 (A), SW49.2
unnamed: D50.2 (A), SW50.2
unnamed: D51.2 (A), SW51.2
unnamed: D52.2 (A), SW52.2
unnamed: D53.2 (A), SW53.2
unnamed: D54.2 (A), SW54.2
unnamed: D55.2 (A), SW55.2
unnamed: D56.2 (A), SW56.2
unnamed: D57.2 (A), SW57.2
unnamed: D58.2 (A), SW58.2
unnamed: D59.2 (A), SW59.2
unnamed: D60.2 (A), SW60.2
unnamed: D61.2 (A), SW61.2
ROW_0: A1.21 (GPIO16), D1.1 (K), D2.1 (K), D3.1 (K), D4.1 (K), D5.1 (K), D6.1 (K), D7.1 (K), D8.1 (K), D9.1 (K), D10.1 (K), D11.1 (K), D12.1 (K), D13.1 (K), D14.1 (K)
ROW_1: A1.22 (GPIO17), D15.1 (K), D16.1 (K), D17.1 (K), D18.1 (K), D19.1 (K), D20.1 (K), D21.1 (K), D22.1 (K), D23.1 (K), D24.1 (K), D25.1 (K), D26.1 (K), D27.1 (K), D28.1 (K)
ROW_2: A1.24 (GPIO18), D29.1 (K), D30.1 (K), D31.1 (K), D32.1 (K), D33.1 (K), D34.1 (K), D35.1 (K), D36.1 (K), D37.1 (K), D38.1 (K), D39.1 (K), D40.1 (K), D41.1 (K)
ROW_3: A1.25 (GPIO19), D42.1 (K), D43.1 (K), D44.1 (K), D45.1 (K), D46.1 (K), D47.1 (K), D48.1 (K), D49.1 (K), D50.1 (K), D51.1 (K), D52.1 (K), D53.1 (K)
ROW_4: A1.26 (GPIO20), D54.1 (K), D55.1 (K), D56.1 (K), D57.1 (K), D58.1 (K), D59.1 (K), D60.1 (K), D61.1 (K)
SCL: A1.1 (GPIO0), J1.4, J2.4, J3.4, J4.4, J5.4, J6.4
SDA: A1.2 (GPIO1), J1.3, J2.3, J3.3, J4.3, J5.3, J6.3

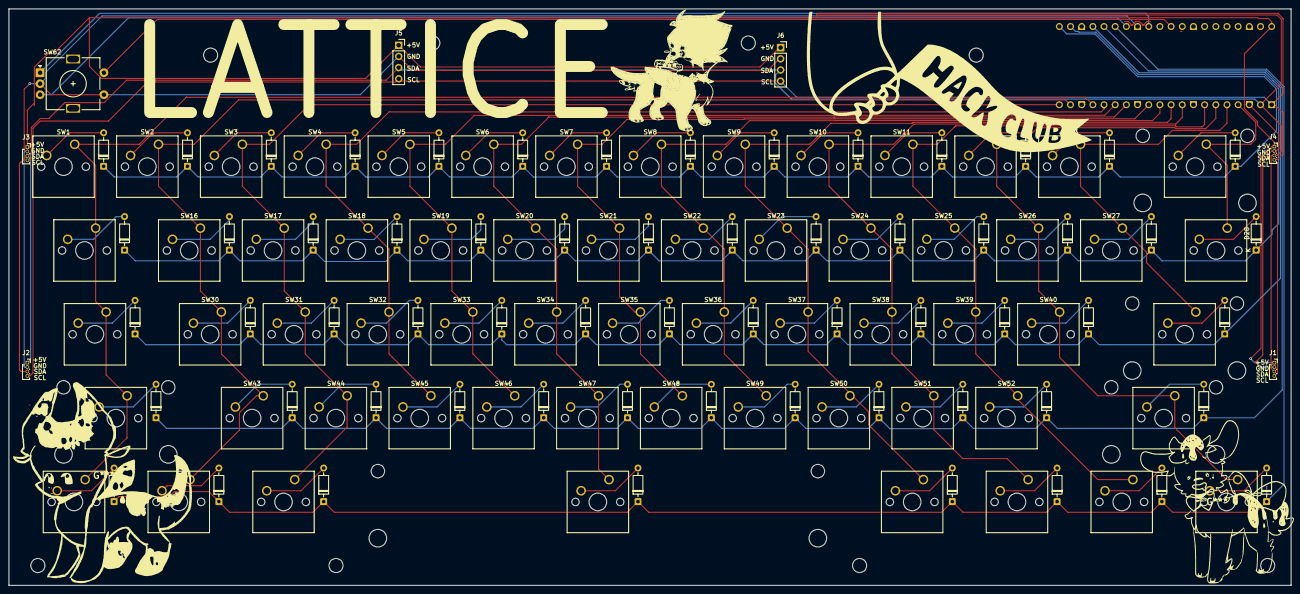
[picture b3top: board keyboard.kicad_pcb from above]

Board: 2 copper layers, 291.4 x 131.0 mm, 138 parts (1 on the bottom side), 87 nets.

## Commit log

2026-05-31 jiggu
2026-06-05 reorganization
2026-06-05 full re-org + readme updates
2026-06-05 README updates
2026-06-05 aaaa
2026-06-05 firmware finish
2026-06-06 add instructions
2026-06-06 oops forgot to commit BOM
2026-06-08 BOM issue
2026-06-08 fix BOM
